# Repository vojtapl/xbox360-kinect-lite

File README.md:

# Pcb and Case for Shrinking the Xbox 360 Kinect
This repository contains a PCB and a basic case for using only the camera board from the Xbox 360 Kinect.

I have recently read [this great article](https://medium.com/robotics-weekends/how-to-turn-old-kinect-into-a-compact-usb-powered-rgbd-sensor-f23d58e10eb0), which lays out the idea of making a *Kinect Lite* from an old Xbox 360 Kinect by isolating the camera board, which can function separately. As I saw one being sold for next to nothing with a broken tilt motor, I thought it would be a great idea to implement the ideas mentioned in the article. The repository contains the PCB (including LCSC part numbers), which generates all the necessary voltage rails, and a basic 3D-printable case.

## What might need improving
- The case model is a bit crude, as I used this as a opportunity to learn some basics of FreeCAD. Also, the camera PCB screws do not seem to be arranged in a rectangle, so one of the mounting holes might need enlarging.
- The case walls are a bit too long and flex a bit when squeezed.
- I am uncertain whether the fan and the fuse (not really sure what exactly it is) on the IR transmitter is really needed.

## Assembly
0. Acquire the Xbox 360 Kinect, make the PCB, and print the case.
1. Tear down the Kinect. [Example video.](https://youtu.be/PgViFpEWwBA)
2. What we will need from it is the PCB to which the cameras are connected (without the LED, as it connects to a PCB which we will not use), the aluminum chassis with the cameras, the cooling fan, some of the screws and standoffs, and the lens plastic holder with the lenses.
3. Cover the cameras and the IR transmitter with tape and cut the aluminum chassis with a saw next to the cameras. One cut will be next to the two cameras - when looking from the inside - right next to the white plastics, and the other will just remove the bent part next to the IR transmitter. See the photos of how it should look afterward. Remember to clean everything from the shavings.

4. Get the case and add the lenses (note that the IR projector one has a small notch) and insert them into the case. Add the plastic holder on top and screw it in (it might need a corner cut).
5. Insert the PCB correctly onto the camera PCB - either use the standoffs with the included screws and then push the small connector in, or push the connector in first so that the small connector connects to the middle pins (with one row on the left and one on the right unconnected). Now is a good time to test things out.
6. Screw the camera PCB into the cut aluminum chassis and connect the cameras, fan, and the IR transmitter (every cable should be connected by now).
7. Insert the fan with the cable sticking up and the rubber padding away from the air intake.

8. Screw in the chassis assembly.
9. Screw in the back plate, and you are done.

## Frequently Asked Questions

- What to do with the thermistor (see image provided by Bolb347 bellow)? As it connects to the mainboard, which we do not use and it seems to work flawlessly without it, you can throw it out.

## Power consumption
The measurements were made with KWS-2301C, a cheap USB-C power meter.
- Idle

- Running with `freenect-regview`

## Images
On the ruler look at the top scale, as that one is in centimeters.
- View from right

- View from side

- View from above

- New PCB (image provided by Bolb347)

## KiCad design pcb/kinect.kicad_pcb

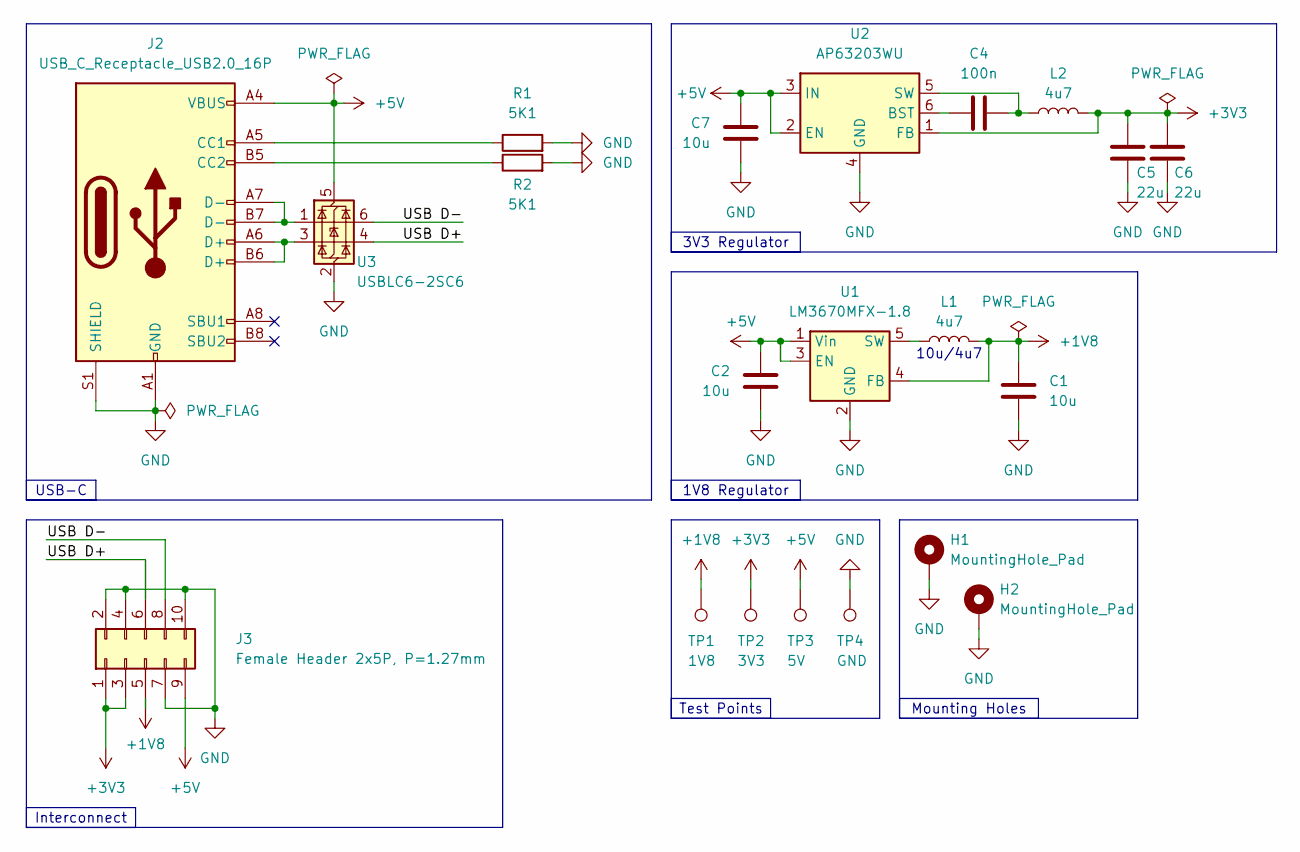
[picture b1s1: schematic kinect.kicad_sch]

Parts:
C1, C2, C7: 10u; C_0603_1608Metric_Pad1.08x0.95mm_HandSolder; LCSC C1691
C4: 100n; C_0603_1608Metric_Pad1.08x0.95mm_HandSolder; LCSC C6119867
C5, C6: 22u; C_0603_1608Metric_Pad1.08x0.95mm_HandSolder; LCSC C59461
H1, H2: MountingHole_Pad; MountingHole_3.2mm_M3_DIN965_Pad
J2: USB_C_Receptacle_USB2.0_16P; USB_C_Receptacle_G-Switch_GT-USB-7010ASV; LCSC C393939
J3: Female Header 2x5P, P=1.27mm; PinSocket_2x05_P1.27mm_Vertical; LCSC C2935883
L1, L2: 4u7; L_1008_2520Metric_Pad1.43x2.20mm_HandSolder; LCSC C315719
R1, R2: 5K1; R_0603_1608Metric_Pad0.98x0.95mm_HandSolder; LCSC C113390
TP1: 1V8; TestPoint_Loop_D2.50mm_Drill1.85mm
TP2: 3V3; TestPoint_Loop_D2.50mm_Drill1.85mm
TP3: 5V; TestPoint_Loop_D2.50mm_Drill1.85mm
TP4: GND; TestPoint_Loop_D2.50mm_Drill1.85mm
U1: LM3670MFX-1.8; TSOT-23-5; LCSC C2071285
U2: AP63203WU; TSOT-23-6; LCSC C780769
U3: USBLC6-2SC6; SOT-23-6_Handsoldering; LCSC C7519

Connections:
+1V8: C1.1, J3.5, L1.2, TP1.1, U1.4 (FB)
+3V3: C5.1, C6.1, J3.1, J3.3, L2.2, TP2.1, U2.1 (FB)
+5V: C2.1, C7.1, J2.A4 (VBUS), J2.A9 (VBUS), J2.B4 (VBUS), J2.B9 (VBUS), J3.9, TP3.1, U1.1 (Vin), U1.3 (EN), U2.2 (EN), U2.3 (IN), U3.5 (VBUS)
/USB D+: J3.6, U3.4 (I/O2)
/USB D-: J3.8, U3.6 (I/O1)
GND: C1.2, C2.2, C5.2, C6.2, C7.2, H1.1, H2.1, J2.A1 (GND), J2.A12 (GND), J2.B1 (GND), J2.B12 (GND), J2.S1 (SHIELD), J3.2, J3.4, J3.7, J3.10, R1.2, R2.2, TP4.1, U1.2 (GND), U2.4 (GND), U3.2 (GND)
unnamed: J2.A5 (CC1), R1.1
unnamed: J2.B5 (CC2), R2.1
unnamed: J2.A6 (D+), J2.B6 (D+), U3.3 (I/O2)
unnamed: J2.A7 (D-), J2.B7 (D-), U3.1 (I/O1)
unnamed: L1.1, U1.5 (SW)
unnamed: C4.2, U2.6 (BST)
unnamed: C4.1, L2.1, U2.5 (SW)

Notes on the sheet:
10u/4u7
USB-C
Interconnect
Test Points
Mounting Holes
1V8 Regulator
3V3 Regulator

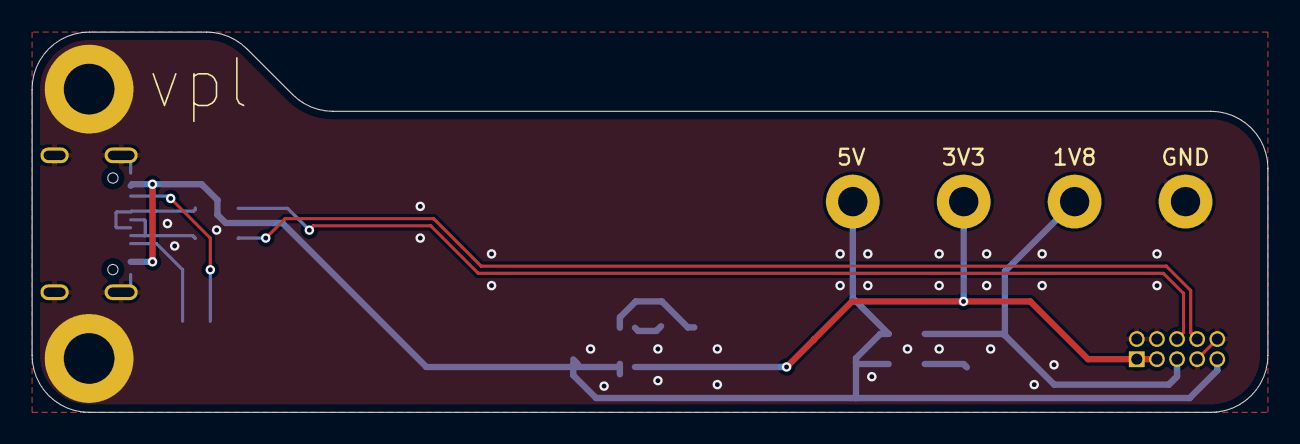
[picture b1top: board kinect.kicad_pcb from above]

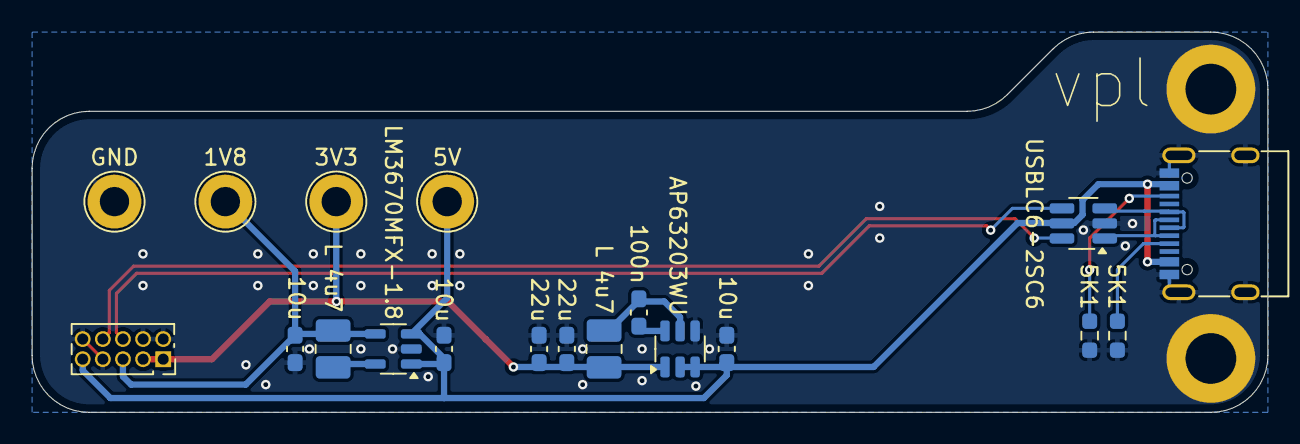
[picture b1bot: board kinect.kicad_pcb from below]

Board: 2 copper layers, 78.0 x 24.0 mm, 21 parts (19 on the bottom side), 13 nets.

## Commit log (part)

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2025-01-16 tried to fix images in README.md
2025-01-16 tried the relative path to fix the images in README.md
2025-01-16 tried the absolute path to fix the images in README.md
2025-02-02 added photos of current consumption
2025-02-02 fixed image URLs and rotations
2025-02-03 added photos of the finished thing
2025-02-10 added photo of pcb
2025-07-21 Beautified the design.
